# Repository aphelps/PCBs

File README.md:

A collection of my board designs.

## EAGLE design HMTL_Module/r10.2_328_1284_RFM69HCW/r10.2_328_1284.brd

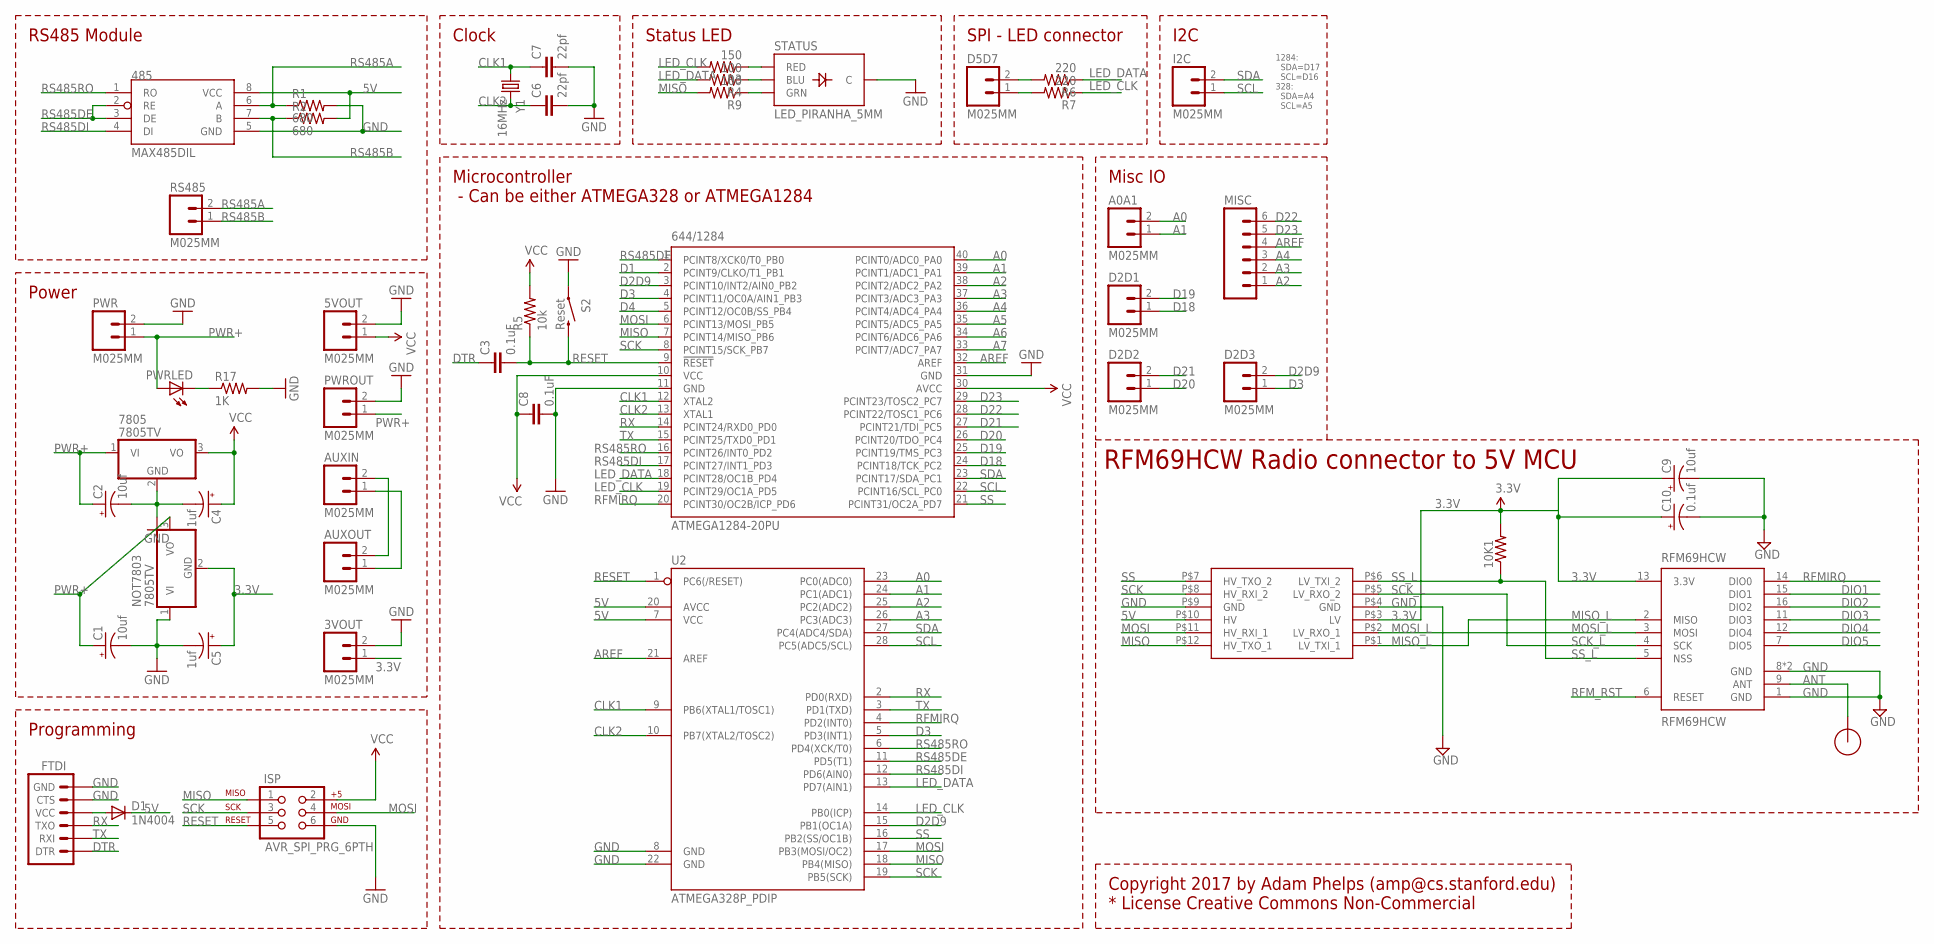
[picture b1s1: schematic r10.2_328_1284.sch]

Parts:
3VOUT, 5VOUT: M025MM; SCREWTERMINAL-5MM-2
10K1: RESISTORPTH-1/4W; AXIAL-0.4
485: MAX485DIL; DIL08
644/1284: ATMEGA1284-20PU; DIL40
7805: 7805TV; TO220V
A0A1: M025MM; SCREWTERMINAL-5MM-2
AUXIN: M025MM; SCREWTERMINAL-5MM-2
AUXOUT: M025MM; SCREWTERMINAL-5MM-2
C1, C2, C9: 10uf; CPOL-RADIAL-10UF-25V
C3, C8: 0.1uF; CAP-PTH-SMALL
C4, C5: 1uf; CPOL-RADIAL-10UF-25V
C6, C7: 22pf; CAP-PTH-SMALL
C10: 0.1uf; CPOL-RADIAL-10UF-25V
D1: 1N4004; DO41-10
D2D1, D2D2, D2D3, D5D7: M025MM; SCREWTERMINAL-5MM-2
FTDI: ARDUINO_SERIAL_PROGRAMPTH; 1X06
I2C: M025MM; SCREWTERMINAL-5MM-2
ISP: AVR_SPI_PRG_6PTH; 2X3
LEVELCONVERTER1: LOGIC_LEVEL_CONVERTER
MISC: M06NO_SILK; 1X06_NO_SILK
NOT7803: 7805TV; TO220V
PWR: M025MM; SCREWTERMINAL-5MM-2
PWRLED: LED5MM
PWROUT: M025MM; SCREWTERMINAL-5MM-2
R1, R2: 680; AXIAL-0.4
R3: 150; AXIAL-0.4
R4, R9: 100; AXIAL-0.4
R5: 10k; AXIAL-0.4
R6, R7: 220; AXIAL-0.4
R17: 1K; AXIAL-0.4
RFM69HCW: RFM69HCW; RFM69HCW-XXXS2
RS485: M025MM; SCREWTERMINAL-5MM-2
S2: Reset; TACTILE_SWITCH_SMD
STATUS: LED_PIRANHA_5MM
U2: ATMEGA328P_PDIP; DIL28-3
U$2: RFM12B_ANTENNA; RFM12B-ANTENNA
Y1: 16MHz; HC49US

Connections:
3.3V: 3VOUT.1, 10K1.P$2 (2), C5.1 (+), C9.1 (+), C10.1 (+), LEVELCONVERTER1.P$3 (LV), NOT7803.2 (GND), RFM69HCW.13 (3.3V)
5V: 5VOUT.1, 485.8 (VCC), 644/1284.10 (VCC), 644/1284.30 (AVCC), 7805.3 (VO), C4.1 (+), C8.1, D1.C, ISP.2, LEVELCONVERTER1.P$10 (HV), R2.P$2 (2), R5.P$2 (2), U2.7 (VCC), U2.20 (AVCC)
A0: 644/1284.40 (PCINT0/ADC0_PA0), A0A1.2, U2.23 (PC0(ADC0))
A1: 644/1284.39 (PCINT1/ADC1_PA1), A0A1.1, U2.24 (PC1(ADC1))
A2: 644/1284.38 (PCINT2/ADC2_PA2), MISC.1, U2.25 (PC2(ADC2))
A3: 644/1284.37 (PCINT3/ADC3_PA3), MISC.2, U2.26 (PC3(ADC3))
A4: 644/1284.36 (PCINT4/ADC4_PA4), MISC.3
A5: 644/1284.35 (PCINT5/ADC5_PA5)
A6: 644/1284.34 (PCINT6/ADC6_PA6)
A7: 644/1284.33 (PCINT7/ADC7_PA7)
ANT: RFM69HCW.9 (ANT), U$2.P$1
AREF: 644/1284.32 (AREF), MISC.4, U2.21 (AREF)
CLK1: 644/1284.12 (XTAL2), C7.1, U2.9 (PB6(XTAL1/TOSC1)), Y1.1
CLK2: 644/1284.13 (XTAL1), C6.1, U2.10 (PB7(XTAL2/TOSC2)), Y1.2
D1: 644/1284.2 (PCINT9/CLKO/T1_PB1)
D2D9: 644/1284.3 (PCINT10/INT2/AIN0_PB2), D2D3.2, U2.15 (PB1(OC1A))
D3: 644/1284.4 (PCINT11/OC0A/AIN1_PB3), D2D3.1, U2.5 (PD3(INT1))
D4: 644/1284.5 (PCINT12/OC0B/SS_PB4)
D18: 644/1284.24 (PCINT18/TCK_PC2), D2D1.1
D19: 644/1284.25 (PCINT19/TMS_PC3), D2D1.2
D20: 644/1284.26 (PCINT20/TDO_PC4), D2D2.1
D21: 644/1284.27 (PCINT21/TDI_PC5), D2D2.2
D22: 644/1284.28 (PCINT22/TOSC1_PC6), MISC.6
D23: 644/1284.29 (PCINT23/TOSC2_PC7), MISC.5
DIO1: RFM69HCW.15 (DIO1)
DIO2: RFM69HCW.16 (DIO2)
DIO3: RFM69HCW.11 (DIO3)
DIO4: RFM69HCW.12 (DIO4)
DIO5: RFM69HCW.7 (DIO5)
DTR: C3.1, FTDI.DTR
GND: 3VOUT.2, 5VOUT.2, 485.5 (GND), 644/1284.11 (GND), 644/1284.31 (GND), 7805.2 (GND), C1.2 (-), C2.2 (-), C4.2 (-), C5.2 (-), C6.2, C7.2, C8.2, C9.2 (-), C10.2 (-), FTDI.CTS, FTDI.GND, ISP.6, LEVELCONVERTER1.P$4 (GND), LEVELCONVERTER1.P$9 (GND), NOT7803.1 (VI), PWR.2, PWROUT.2, R1.P$2 (2), R17.P$2 (2), RFM69HCW.1 (GND), RFM69HCW.8 (GND), RFM69HCW.10 (GND), S2.1, STATUS.- (C), U2.8 (GND), U2.22 (GND)
LED_CLK: 644/1284.19 (PCINT29/OC1A_PD5), R3.P$2 (2), R7.P$1 (1), U2.14 (PB0(ICP))
LED_DATA: 644/1284.18 (PCINT28/OC1B_PD4), R4.P$2 (2), R6.P$1 (1), U2.13 (PD7(AIN1))
MISO: 644/1284.7 (PCINT14/MISO_PB6), ISP.1, LEVELCONVERTER1.P$12 (HV_TXO_1), R9.P$2 (2), U2.18 (PB4(MISO))
MISO_L: LEVELCONVERTER1.P$1 (LV_TXI_1), RFM69HCW.2 (MISO)
MOSI: 644/1284.6 (PCINT13/MOSI_PB5), ISP.4, LEVELCONVERTER1.P$11 (HV_RXI_1), U2.17 (PB3(MOSI/OC2))
MOSI_L: LEVELCONVERTER1.P$2 (LV_RXO_1), RFM69HCW.3 (MOSI)
unnamed: PWRLED.K (C), R17.P$1 (1)
unnamed: AUXIN.1, AUXOUT.1
unnamed: AUXIN.2, AUXOUT.2
unnamed: D5D7.2, R6.P$2 (2)
unnamed: R3.P$1 (1), STATUS.R (RED)
unnamed: R4.P$1 (1), STATUS.B (BLU)
unnamed: R9.P$1 (1), STATUS.G (GRN)
unnamed: D5D7.1, R7.P$2 (2)
unnamed: D1.A, FTDI.VCC
PWR+: 7805.1 (VI), C1.1 (+), C2.1 (+), NOT7803.3 (VO), PWR.1, PWRLED.A, PWROUT.1
RESET: 644/1284.9 (!RESET), C3.2, ISP.5, R5.P$1 (1), S2.3 (2), U2.1 (PC6(/RESET))
RFMIRQ: 644/1284.20 (PCINT30/OC2B/ICP_PD6), RFM69HCW.14 (DIO0), U2.4 (PD2(INT0))
RFM_RST: RFM69HCW.6 (RESET)
RS485A: 485.6 (A), R1.P$1 (1), RS485.2
RS485B: 485.7 (B), R2.P$1 (1), RS485.1
RS485DE: 485.2 (RE), 485.3 (DE), 644/1284.1 (PCINT8/XCK0/T0_PB0), U2.11 (PD5(T1))
RS485DI: 485.4 (DI), 644/1284.17 (PCINT27/INT1_PD3), U2.12 (PD6(AIN0))
RS485RO: 485.1 (RO), 644/1284.16 (PCINT26/INT0_PD2), U2.6 (PD4(XCK/T0))
RX: 644/1284.14 (PCINT24/RXD0_PD0), FTDI.TXO, U2.2 (PD0(RXD))
SCK: 644/1284.8 (PCINT15/SCK_PB7), ISP.3, LEVELCONVERTER1.P$8 (HV_RXI_2), U2.19 (PB5(SCK))
SCK_L: LEVELCONVERTER1.P$5 (LV_RXO_2), RFM69HCW.4 (SCK)
SCL: 644/1284.22 (PCINT16/SCL_PC0), I2C.1, U2.28 (PC5(ADC5/SCL))
SDA: 644/1284.23 (PCINT17/SDA_PC1), I2C.2, U2.27 (PC4(ADC4/SDA))
SS: 644/1284.21 (PCINT31/OC2A_PD7), LEVELCONVERTER1.P$7 (HV_TXO_2), U2.16 (PB2(SS/OC1B))
SS_L: 10K1.P$1 (1), LEVELCONVERTER1.P$6 (LV_TXI_2), RFM69HCW.5 (NSS)
TX: 644/1284.15 (PCINT25/TXD0_PD1), FTDI.RXI, U2.3 (PD1(TXD))

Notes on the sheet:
RS485 Module
Programming
Power
Clock
Status LED
Microcontroller - Can be either ATMEGA328 or ATMEGA1284
SPI - LED connector
Copyright 2017 by Adam Phelps (amp@cs.stanford.edu) * License Creative Commons Non-Commercial
I2C
1284: SDA=D17 SCL=D16 328: SDA=A4 SCL=A5
Misc IO
RFM69HCW Radio connector to 5V MCU

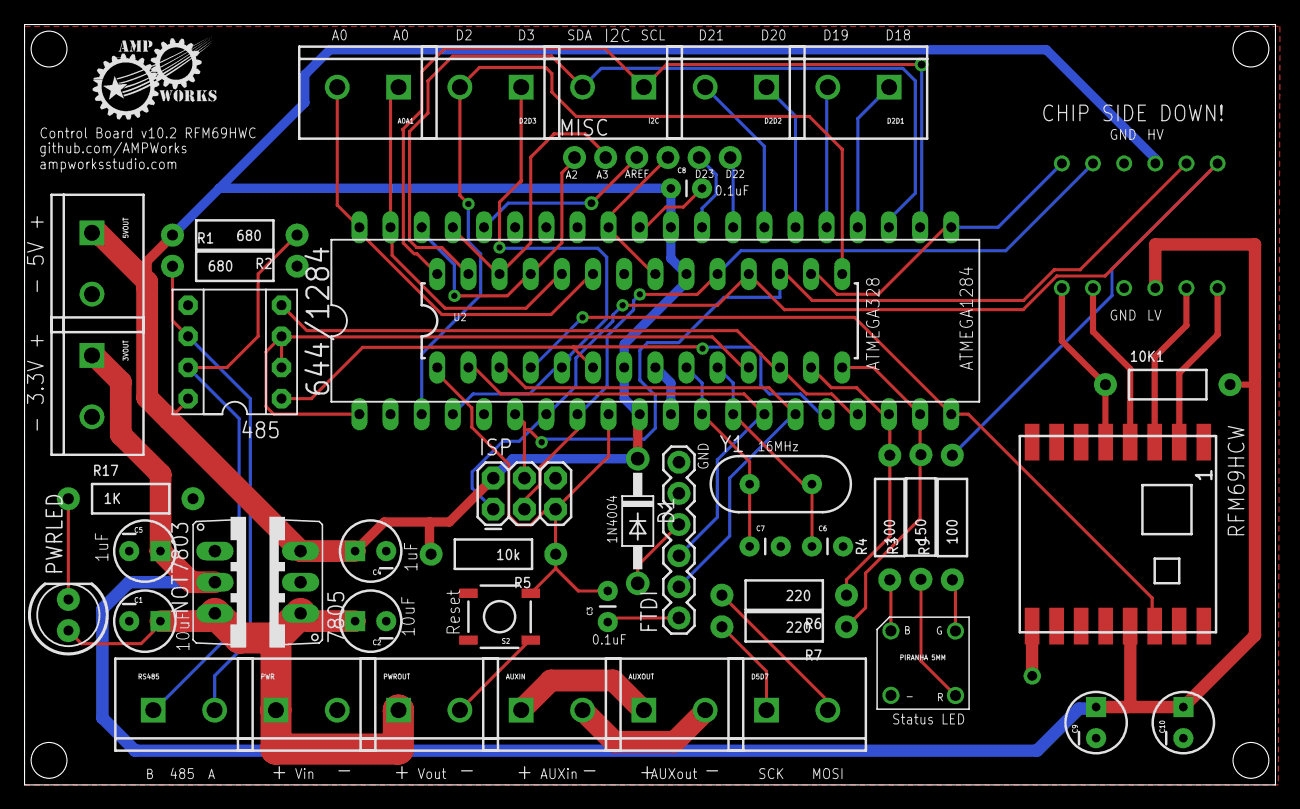
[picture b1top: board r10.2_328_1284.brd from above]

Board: 2 copper layers, 102.0 x 62.0 mm, 49 parts (1 on the bottom side), 52 nets.

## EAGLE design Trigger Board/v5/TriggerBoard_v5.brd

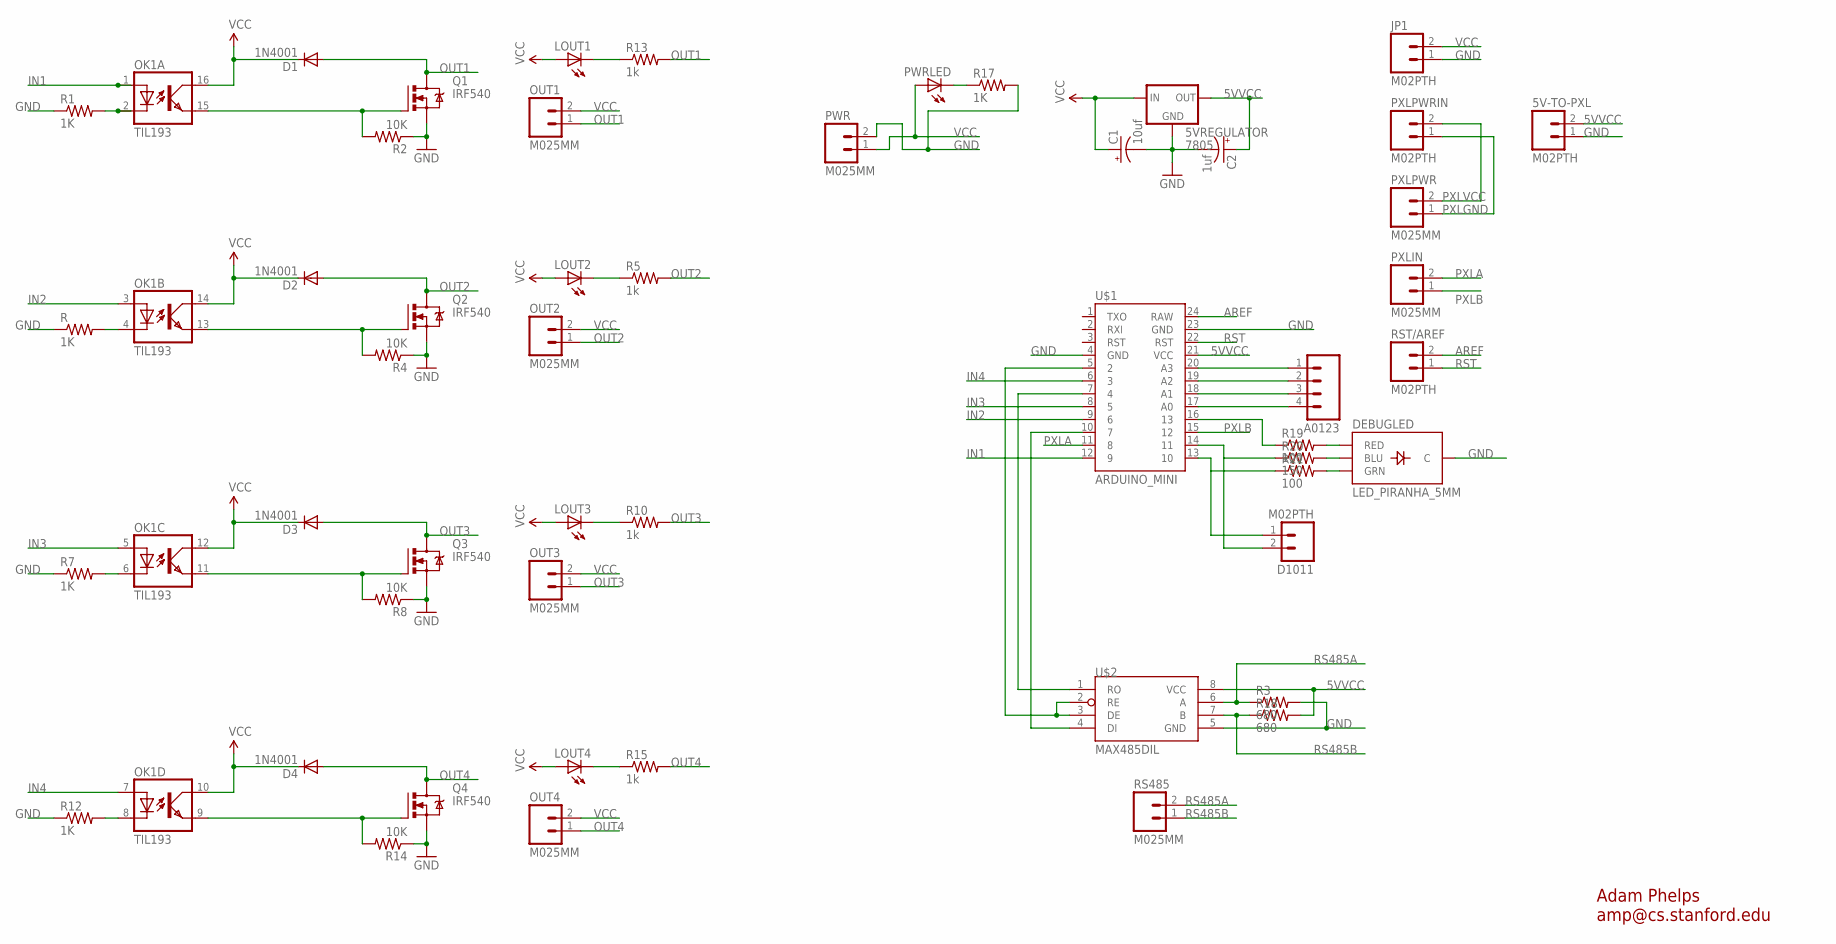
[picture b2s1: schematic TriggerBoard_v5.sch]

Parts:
5V-TO-PXL: M02PTH; 1X02
5VREGULATOR: 7805; TO220-IGO
A0123: M04PTH; 1X04
C1: 10uf; CPOL-RADIAL-10UF-25V
C2: 1uf; CPOL-RADIAL-10UF-25V
D1, D2, D3, D4: 1N4001; DIODE-1N4001
D1011: M02PTH; 1X02
DEBUGLED: LED_PIRANHA_5MM
JP1: M02PTH; 1X02
LOUT1, LOUT2, LOUT3, LOUT4: LED3MM
OK1: TIL193; DIL16
OUT1, OUT2, OUT3, OUT4: M025MM; SCREWTERMINAL-5MM-2
PWR: M025MM; SCREWTERMINAL-5MM-2
PWRLED: LED5MM
PXLIN: M025MM; SCREWTERMINAL-5MM-2
PXLPWR: M025MM; SCREWTERMINAL-5MM-2
PXLPWRIN: M02PTH; 1X02
Q1, Q2, Q3, Q4: IRF540; TO220BV
R, R1, R7, R12, R17: 1K; AXIAL-0.4
R2, R4, R8, R14: 10K; AXIAL-0.4
R3, R18: 680; AXIAL-0.4
R5, R10, R13, R15: 1k; AXIAL-0.4
R19, R21: 100; AXIAL-0.4
R20: 150; AXIAL-0.4
RS485: M025MM; SCREWTERMINAL-5MM-2
RST/AREF: M02PTH; 1X02
U$1: ARDUINO_MINI
U$2: MAX485DIL; DIL08

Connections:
5VVCC: 5V-TO-PXL.2, 5VREGULATOR.OUT, C2.1 (+), R18.P$2 (2), U$1.21 (VCC), U$2.8 (VCC)
AREF: RST/AREF.2, U$1.24 (RAW)
GND: 5V-TO-PXL.1, 5VREGULATOR.GND, C1.2 (-), C2.2 (-), DEBUGLED.- (C), JP1.1, PWR.2, Q1.S, Q2.S, Q3.S, Q4.S, R.P$1 (1), R1.P$1 (1), R2.P$1 (1), R3.P$2 (2), R4.P$1 (1), R7.P$1 (1), R8.P$1 (1), R12.P$1 (1), R14.P$1 (1), R17.P$2 (2), U$1.4 (GND), U$1.23 (GND), U$2.5 (GND)
IN1: OK1.1 (A), U$1.12 (9)
IN2: OK1.3 (A), U$1.9 (6)
IN3: OK1.5 (A), U$1.8 (5)
IN4: OK1.7 (A), U$1.6 (3)
unnamed: LOUT1.K (C), R13.P$1 (1)
unnamed: OK1.4 (C), R.P$2 (2)
unnamed: A0123.4, U$1.17 (A0)
unnamed: OK1.15 (EMIT), Q1.G, R2.P$2 (2)
unnamed: OK1.13 (EMIT), Q2.G, R4.P$2 (2)
unnamed: OK1.2 (C), R1.P$2 (2)
unnamed: LOUT2.K (C), R5.P$1 (1)
unnamed: D1011.1, R21.P$1 (1), U$1.13 (10)
unnamed: OK1.11 (EMIT), Q3.G, R8.P$2 (2)
unnamed: LOUT3.K (C), R10.P$1 (1)
unnamed: OK1.6 (C), R7.P$2 (2)
unnamed: D1011.2, R20.P$1 (1), U$1.14 (11)
unnamed: OK1.9 (EMIT), Q4.G, R14.P$2 (2)
unnamed: LOUT4.K (C), R15.P$1 (1)
unnamed: OK1.8 (C), R12.P$2 (2)
unnamed: R19.P$1 (1), U$1.16 (13)
unnamed: PWRLED.K (C), R17.P$1 (1)
unnamed: A0123.3, U$1.18 (A1)
unnamed: U$1.5 (2), U$2.2 (RE), U$2.3 (DE)
unnamed: U$1.7 (4), U$2.1 (RO)
unnamed: U$1.10 (7), U$2.4 (DI)
unnamed: DEBUGLED.R (RED), R19.P$2 (2)
unnamed: DEBUGLED.B (BLU), R20.P$2 (2)
unnamed: DEBUGLED.G (GRN), R21.P$2 (2)
unnamed: A0123.2, U$1.19 (A2)
unnamed: A0123.1, U$1.20 (A3)
OUT1: D1.A, OUT1.1, Q1.D, R13.P$2 (2)
OUT2: D2.A, OUT2.1, Q2.D, R5.P$2 (2)
OUT3: D3.A, OUT3.1, Q3.D, R10.P$2 (2)
OUT4: D4.A, OUT4.1, Q4.D, R15.P$2 (2)
PXLA: PXLIN.2, U$1.11 (8)
PXLB: PXLIN.1, U$1.15 (12)
PXLGND: PXLPWR.1, PXLPWRIN.1
PXLVCC: PXLPWR.2, PXLPWRIN.2
RS485A: R3.P$1 (1), RS485.2, U$2.6 (A)
RS485B: R18.P$1 (1), RS485.1, U$2.7 (B)
RST: RST/AREF.1, U$1.22 (RST)
VCC: 5VREGULATOR.IN, C1.1 (+), D1.C, D2.C, D3.C, D4.C, JP1.2, LOUT1.A, LOUT2.A, LOUT3.A, LOUT4.A, OK1.10 (COL), OK1.12 (COL), OK1.14 (COL), OK1.16 (COL), OUT1.2, OUT2.2, OUT3.2, OUT4.2, PWR.1, PWRLED.A

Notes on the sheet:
Adam Phelps amp@cs.stanford.edu

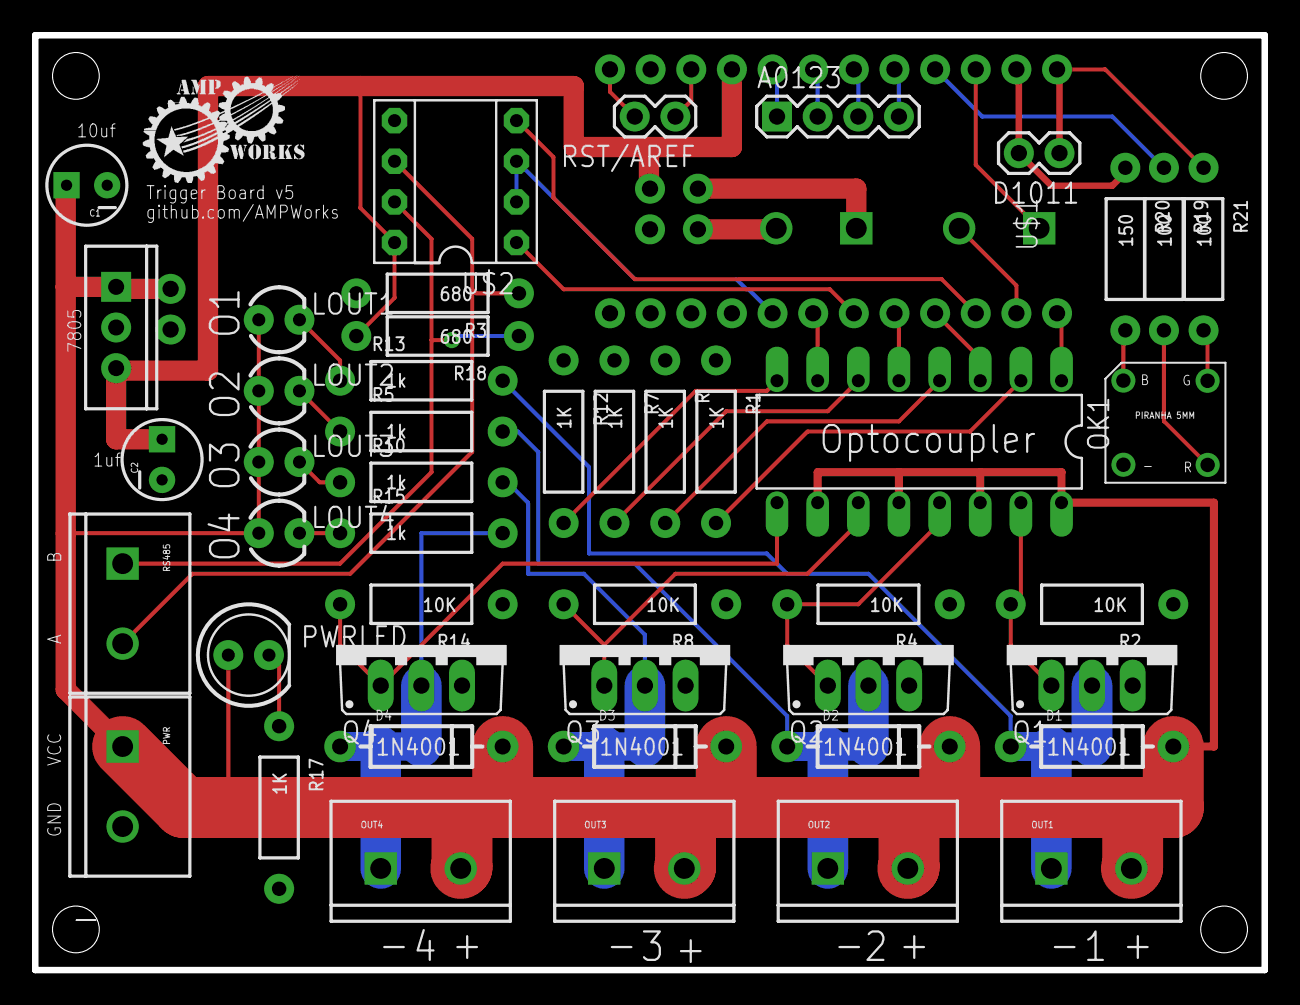
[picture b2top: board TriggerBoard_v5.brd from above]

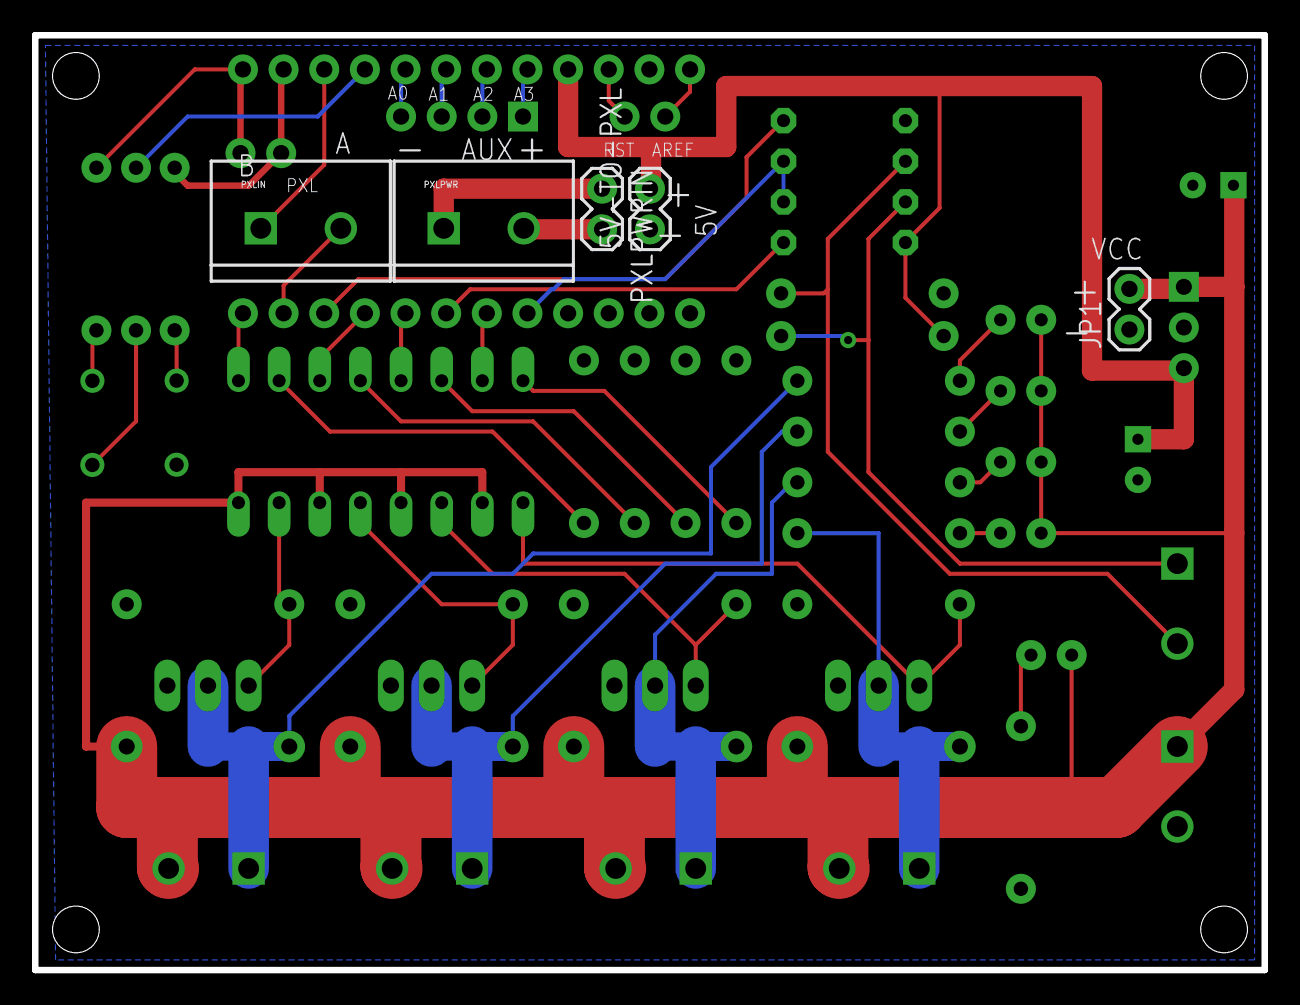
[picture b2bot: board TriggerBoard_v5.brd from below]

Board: 2 copper layers, 76.8 x 58.4 mm, 52 parts (5 on the bottom side), 45 nets.

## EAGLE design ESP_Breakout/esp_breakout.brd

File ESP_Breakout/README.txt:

This board is for connecting an ESP8266 to a 5V MCU

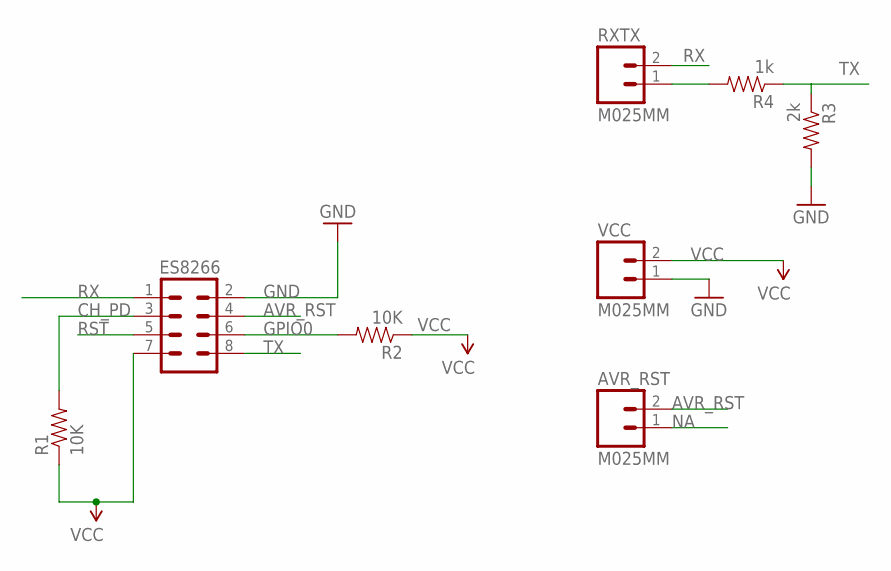
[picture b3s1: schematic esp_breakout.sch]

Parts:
AVR_RST: M025MM; SCREWTERMINAL-5MM-2
ES8266: M04X2; 2X4
R1, R2: 10K; AXIAL-0.3
R3: 2k; AXIAL-0.3
R4: 1k; AXIAL-0.3
RXTX: M025MM; SCREWTERMINAL-5MM-2
VCC: M025MM; SCREWTERMINAL-5MM-2

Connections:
AVR_RST: AVR_RST.2, ES8266.4
CH_PD: ES8266.3, R1.P$2 (2)
GND: ES8266.2, R3.P$2 (2), VCC.1
GPIO0: ES8266.6, R2.P$2 (2)
unnamed: R4.P$2 (2), RXTX.1
NA: AVR_RST.1
RST: ES8266.5
RX: ES8266.1, RXTX.2
TX: ES8266.8, R3.P$1 (1), R4.P$1 (1)
VCC: ES8266.7, R1.P$1 (1), R2.P$1 (1), VCC.2

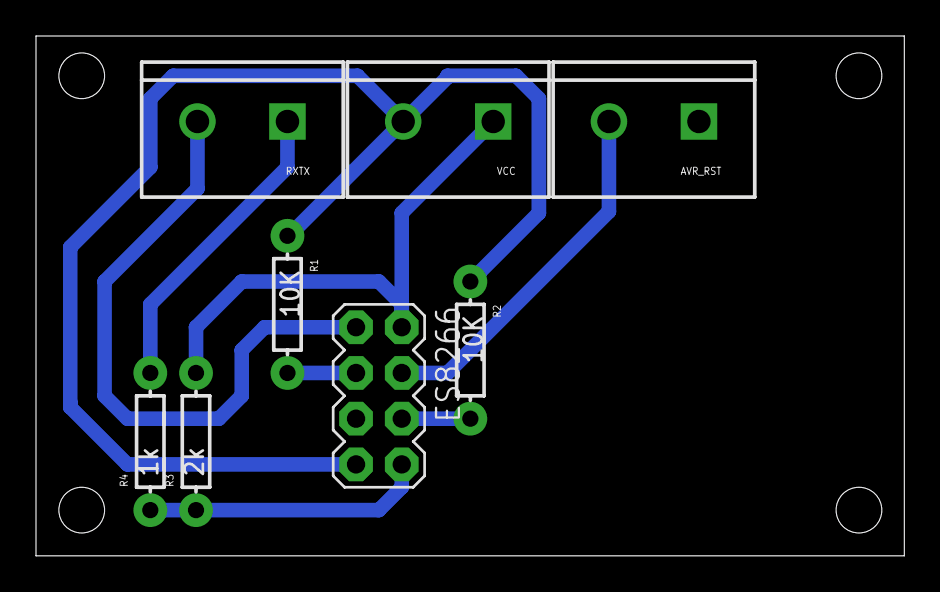
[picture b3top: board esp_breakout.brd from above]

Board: 2 copper layers, 48.2 x 28.9 mm, 8 parts (0 on the bottom side), 8 nets.

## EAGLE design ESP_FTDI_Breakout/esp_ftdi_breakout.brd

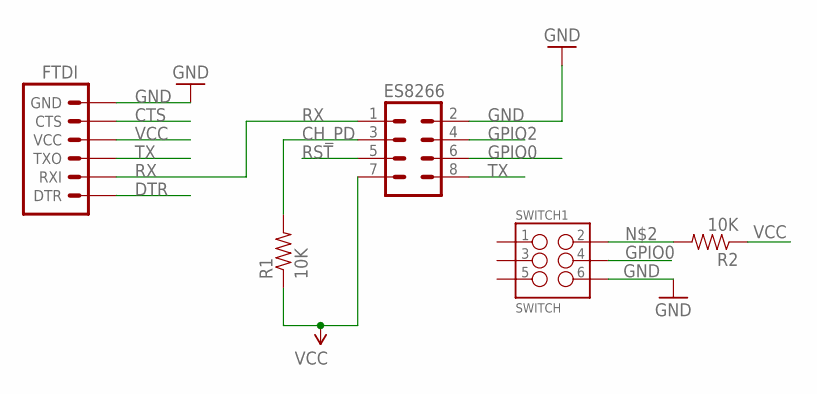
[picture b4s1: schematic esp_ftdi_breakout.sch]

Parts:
ES8266: M04X2; 2X4
FTDI: ARDUINO_SERIAL_PROGRAMPTH; 1X06
R1, R2: 10K; AXIAL-0.3
SWITCH1: SWITCH; 2X3

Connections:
CH_PD: ES8266.3, R1.P$2 (2)
CTS: FTDI.5 (CTS)
DTR: FTDI.1 (DTR)
GND: ES8266.2, FTDI.6 (GND), SWITCH1.6
GPIO0: ES8266.6, SWITCH1.4
GPIO2: ES8266.4
unnamed: R2.P$2 (2), SWITCH1.2
RST: ES8266.5
RX: ES8266.1, FTDI.2 (RXI)
TX: ES8266.8, FTDI.3 (TXO)
VCC: ES8266.7, FTDI.4 (VCC), R1.P$1 (1), R2.P$1 (1)

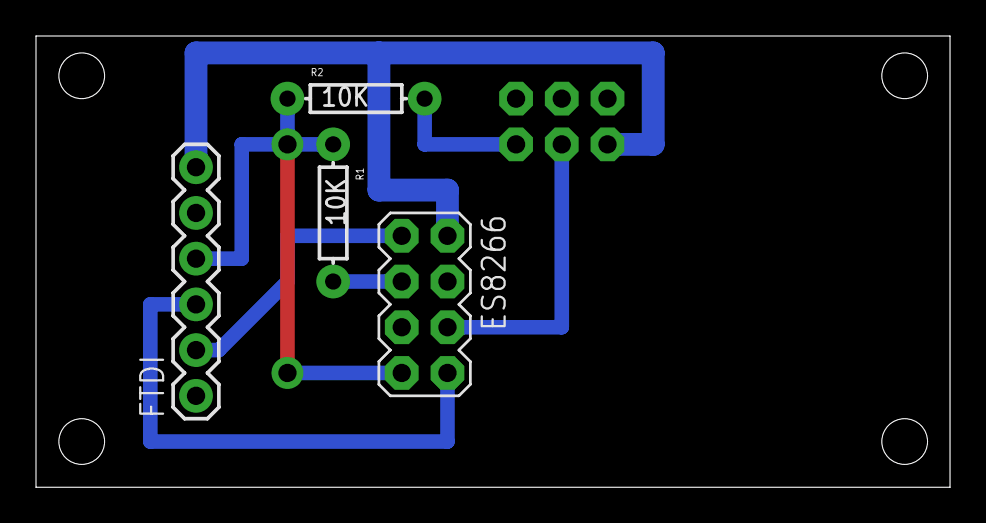
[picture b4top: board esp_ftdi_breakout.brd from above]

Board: 2 copper layers, 50.8 x 25.1 mm, 5 parts (1 on the bottom side), 7 nets.

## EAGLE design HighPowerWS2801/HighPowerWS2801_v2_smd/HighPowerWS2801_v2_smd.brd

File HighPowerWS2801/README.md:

Addressable high-power LED drivers

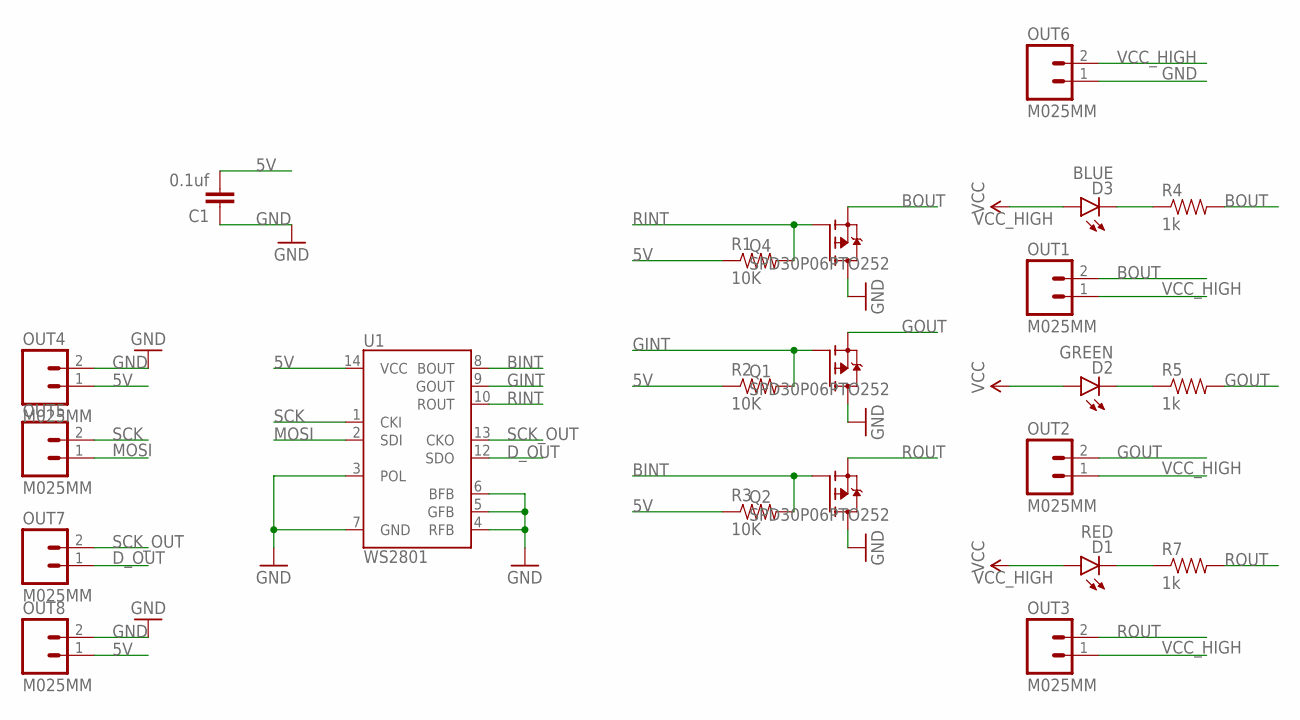
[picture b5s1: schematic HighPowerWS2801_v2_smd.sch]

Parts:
C1: 0.1uf; 0603-CAP
D1: RED; LED-0603
D2: GREEN; LED-0603
D3: BLUE; LED-0603
OUT1, OUT2, OUT3, OUT4, OUT5, OUT6, OUT7, OUT8: M025MM; SCREWTERMINAL-5MM-2
Q1, Q2, Q4: SPD30P06PTO252; TO252
R1, R2, R3: 10K; 0603-RES
R4, R5, R7: 1k; 0603-RES
U1: WS2801; SOP-14

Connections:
5V: C1.2, OUT4.1, OUT8.1, R1.1, R2.1, R3.1, U1.14 (VCC)
BINT: Q2.1 (G), R3.2, U1.8 (BOUT)
BOUT: OUT1.2, Q4.2 (S), R4.2
D_OUT: OUT7.1, U1.12 (SDO)
GINT: Q1.1 (G), R2.2, U1.9 (GOUT)
GND: C1.1, OUT4.2, OUT6.1, OUT8.2, Q1.3 (D), Q2.3 (D), Q4.3 (D), U1.3 (POL), U1.4 (RFB), U1.5 (GFB), U1.6 (BFB), U1.7 (GND)
GOUT: OUT2.2, Q1.2 (S), R5.2
MOSI: OUT5.1, U1.2 (SDI)
unnamed: D3.C, R4.1
unnamed: D2.C, R5.1
unnamed: D1.C, R7.1
RINT: Q4.1 (G), R1.2, U1.10 (ROUT)
ROUT: OUT3.2, Q2.2 (S), R7.2
SCK: OUT5.2, U1.1 (CKI)
SCK_OUT: OUT7.2, U1.13 (CKO)
VCC_HIGH: D1.A, D2.A, D3.A, OUT1.1, OUT2.1, OUT3.1, OUT6.2

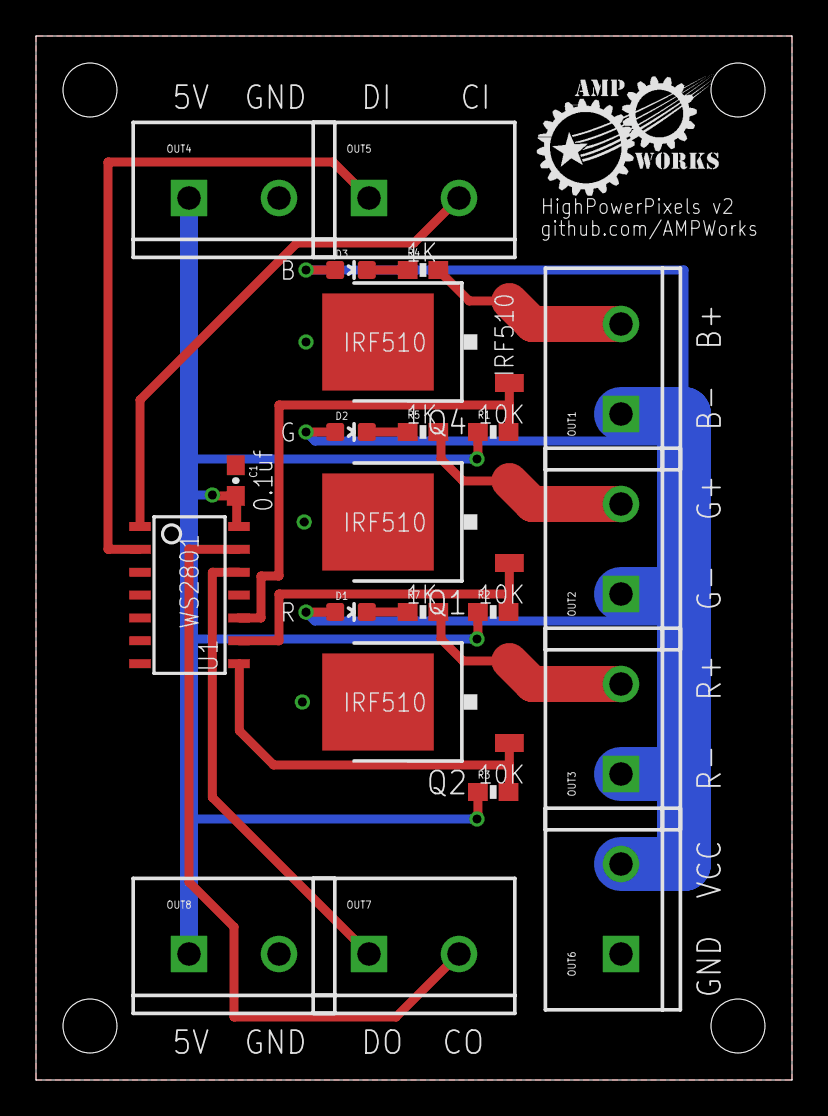
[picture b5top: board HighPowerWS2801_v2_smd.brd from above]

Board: 2 copper layers, 42.0 x 58.0 mm, 22 parts (0 on the bottom side), 16 nets.

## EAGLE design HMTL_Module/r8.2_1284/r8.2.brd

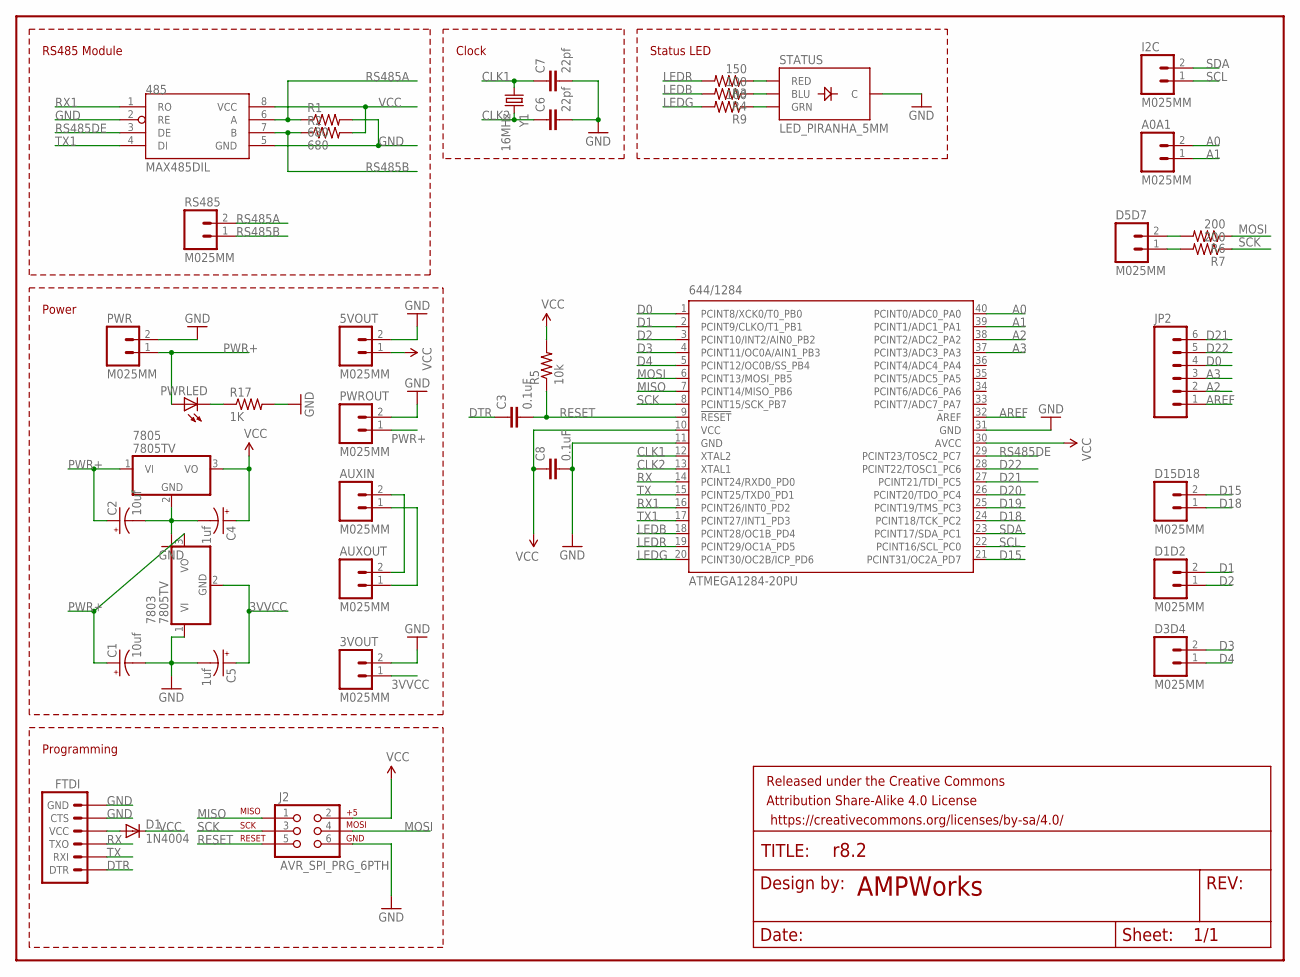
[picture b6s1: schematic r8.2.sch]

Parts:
3VOUT, 5VOUT: M025MM; SCREWTERMINAL-5MM-2
485: MAX485DIL; DIL08
644/1284: ATMEGA1284-20PU; DIL40
7803, 7805: 7805TV; TO220V
A0A1: M025MM; SCREWTERMINAL-5MM-2
AUXIN: M025MM; SCREWTERMINAL-5MM-2
AUXOUT: M025MM; SCREWTERMINAL-5MM-2
C1, C2: 10uf; CPOL-RADIAL-10UF-25V
C3, C8: 0.1uF; CAP-PTH-SMALL
C4, C5: 1uf; CPOL-RADIAL-10UF-25V
C6, C7: 22pf; CAP-PTH-SMALL
D1: 1N4004; DO41-10
D1D2, D3D4, D5D7, D15D18: M025MM; SCREWTERMINAL-5MM-2
FRAME1: FRAME-LETTER; CREATIVE_COMMONS
FTDI: ARDUINO_SERIAL_PROGRAMPTH; 1X06
I2C: M025MM; SCREWTERMINAL-5MM-2
J2: AVR_SPI_PRG_6PTH; 2X3
JP2: M06NO_SILK; 1X06_NO_SILK
PWR: M025MM; SCREWTERMINAL-5MM-2
PWRLED: LED5MM
PWROUT: M025MM; SCREWTERMINAL-5MM-2
R1, R2: 680; AXIAL-0.4
R3: 150; AXIAL-0.4
R4, R9: 100; AXIAL-0.4
R5: 10k; AXIAL-0.4
R6, R7: 200; AXIAL-0.4
R17: 1K; AXIAL-0.4
RS485: M025MM; SCREWTERMINAL-5MM-2
STATUS: LED_PIRANHA_5MM
Y1: 16MHz; HC49US

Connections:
3VVCC: 3VOUT.1, 7803.2 (GND), C5.1 (+)
A0: 644/1284.40 (PCINT0/ADC0_PA0), A0A1.2
A1: 644/1284.39 (PCINT1/ADC1_PA1), A0A1.1
A2: 644/1284.38 (PCINT2/ADC2_PA2), JP2.2
A3: 644/1284.37 (PCINT3/ADC3_PA3), JP2.3
AREF: 644/1284.32 (AREF), JP2.1
CLK1: 644/1284.12 (XTAL2), C7.1, Y1.1
CLK2: 644/1284.13 (XTAL1), C6.1, Y1.2
D0: 644/1284.1 (PCINT8/XCK0/T0_PB0), JP2.4
D1: 644/1284.2 (PCINT9/CLKO/T1_PB1), D1D2.2
D2: 644/1284.3 (PCINT10/INT2/AIN0_PB2), D1D2.1
D3: 644/1284.4 (PCINT11/OC0A/AIN1_PB3), D3D4.2
D4: 644/1284.5 (PCINT12/OC0B/SS_PB4), D3D4.1
D15: 644/1284.21 (PCINT31/OC2A_PD7), D15D18.2
D18: 644/1284.24 (PCINT18/TCK_PC2), D15D18.1
D19: 644/1284.25 (PCINT19/TMS_PC3)
D20: 644/1284.26 (PCINT20/TDO_PC4)
D21: 644/1284.27 (PCINT21/TDI_PC5), JP2.6
D22: 644/1284.28 (PCINT22/TOSC1_PC6), JP2.5
DTR: C3.1, FTDI.DTR
GND: 3VOUT.2, 5VOUT.2, 485.2 (RE), 485.5 (GND), 644/1284.11 (GND), 644/1284.31 (GND), 7803.1 (VI), 7805.2 (GND), C1.2 (-), C2.2 (-), C4.2 (-), C5.2 (-), C6.2, C7.2, C8.2, FTDI.CTS, FTDI.GND, J2.6, PWR.2, PWROUT.2, R1.P$2 (2), R17.P$2 (2), STATUS.- (C)
LEDB: 644/1284.18 (PCINT28/OC1B_PD4), R4.P$2 (2)
LEDG: 644/1284.20 (PCINT30/OC2B/ICP_PD6), R9.P$2 (2)
LEDR: 644/1284.19 (PCINT29/OC1A_PD5), R3.P$2 (2)
MISO: 644/1284.7 (PCINT14/MISO_PB6), J2.1
MOSI: 644/1284.6 (PCINT13/MOSI_PB5), J2.4, R6.P$1 (1)
unnamed: PWRLED.K (C), R17.P$1 (1)
unnamed: AUXIN.1, AUXOUT.1
unnamed: AUXIN.2, AUXOUT.2
unnamed: D5D7.2, R6.P$2 (2)
unnamed: R3.P$1 (1), STATUS.R (RED)
unnamed: R4.P$1 (1), STATUS.B (BLU)
unnamed: R9.P$1 (1), STATUS.G (GRN)
unnamed: D5D7.1, R7.P$2 (2)
unnamed: D1.A, FTDI.VCC
PWR+: 7803.3 (VO), 7805.1 (VI), C1.1 (+), C2.1 (+), PWR.1, PWRLED.A, PWROUT.1
RESET: 644/1284.9 (!RESET), C3.2, J2.5, R5.P$1 (1)
RS485A: 485.6 (A), R1.P$1 (1), RS485.2
RS485B: 485.7 (B), R2.P$1 (1), RS485.1
RS485DE: 485.3 (DE), 644/1284.29 (PCINT23/TOSC2_PC7)
RX: 644/1284.14 (PCINT24/RXD0_PD0), FTDI.TXO
RX1: 485.1 (RO), 644/1284.16 (PCINT26/INT0_PD2)
SCK: 644/1284.8 (PCINT15/SCK_PB7), J2.3, R7.P$1 (1)
SCL: 644/1284.22 (PCINT16/SCL_PC0), I2C.1
SDA: 644/1284.23 (PCINT17/SDA_PC1), I2C.2
TX: 644/1284.15 (PCINT25/TXD0_PD1), FTDI.RXI
TX1: 485.4 (DI), 644/1284.17 (PCINT27/INT1_PD3)
VCC: 5VOUT.1, 485.8 (VCC), 644/1284.10 (VCC), 644/1284.30 (AVCC), 7805.3 (VO), C4.1 (+), C8.1, D1.C, J2.2, R2.P$2 (2), R5.P$2 (2)

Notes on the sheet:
RS485 Module
Programming
Power
AMPWorks
Clock
Status LED

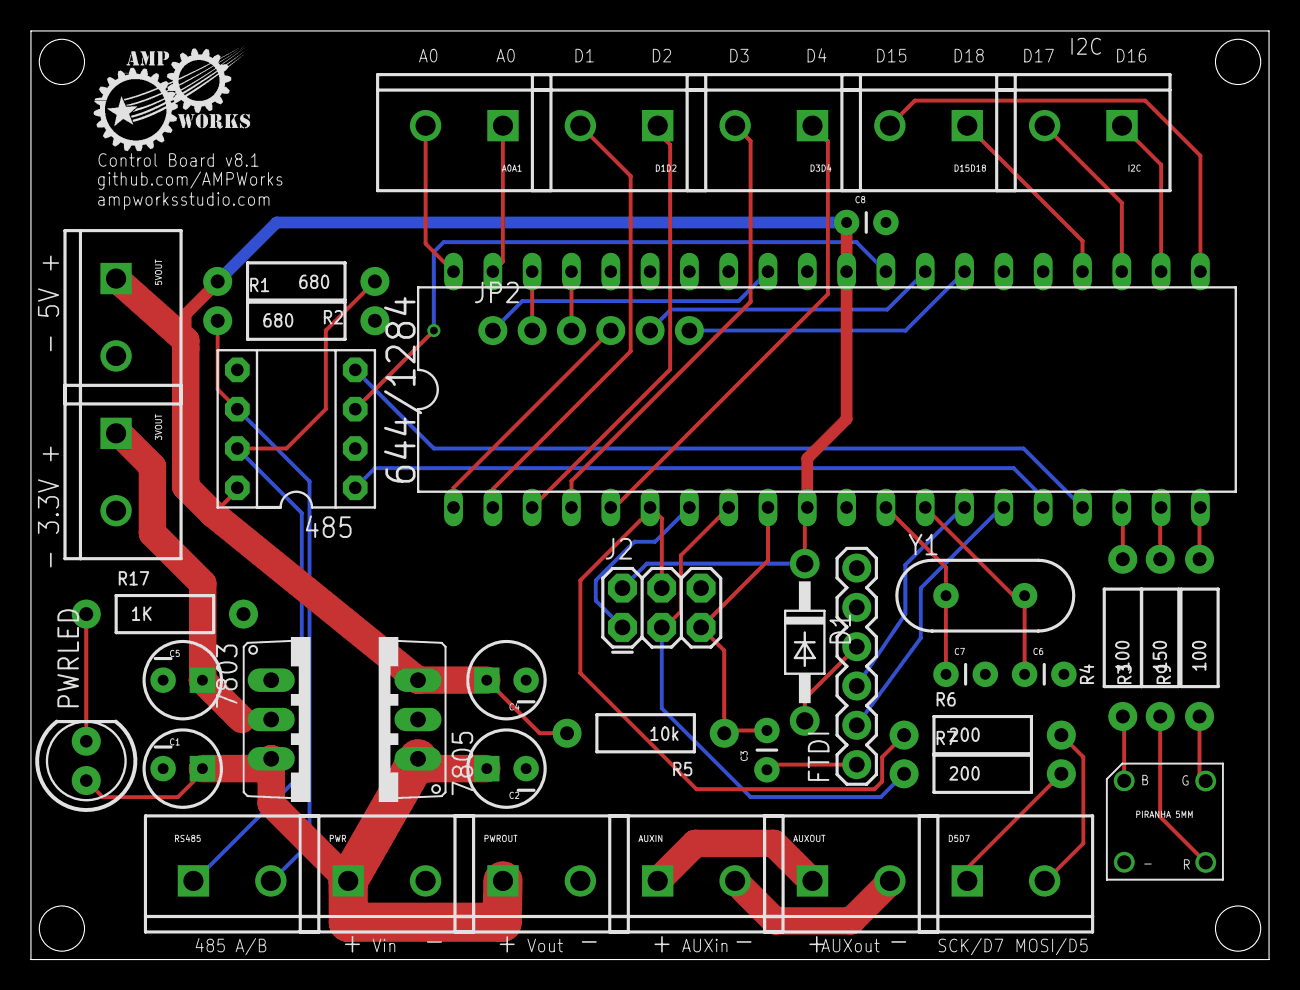
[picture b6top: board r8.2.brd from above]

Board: 2 copper layers, 80.0 x 60.0 mm, 42 parts (0 on the bottom side), 46 nets.

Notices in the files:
parts and their libraries:
SparkFun-Connectors: Licensing: Creative Commons ShareAlike 4.0 International - https://creativecommons.org/licenses/by-sa/4.0
SparkFun-Aesthetics: Released under the Creative Commons Attribution Share-Alike 4.0 License
SparkFun-Aesthetics: https://creativecommons.org/licenses/by-sa/4.0
